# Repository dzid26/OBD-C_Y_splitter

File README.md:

# OBD-C Y-splitter
- compact size - 1x2.5cm
- possibility to add 120ohm CAN termination on CAN1 and CAN3 (note they can flip, so always terminate both)
- test points for sbu1 and sbu2

### Arrangement:
- Female-Male-Female - harness box has to be connected to J1 (as indicated by the arrow's origin)

Schematic:

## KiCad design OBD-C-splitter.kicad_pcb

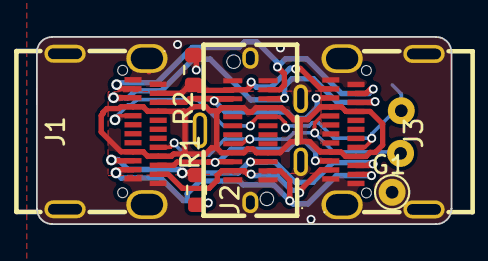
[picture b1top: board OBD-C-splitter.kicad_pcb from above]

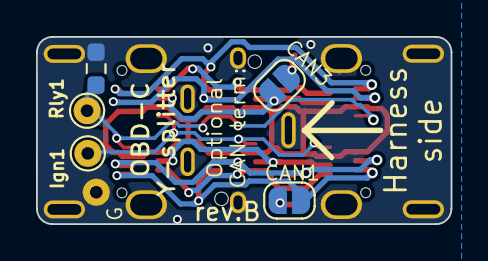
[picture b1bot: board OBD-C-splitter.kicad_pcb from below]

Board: 2 copper layers, 23.0 x 10.4 mm, 11 parts (5 on the bottom side), 14 nets.

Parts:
CAN1, CAN3: SolderJumper_2_Open; SolderJumper-2_P1.3mm_Open_RoundedPad1.0x1.5mm
G1: TestPoint; TestPoint_THTPad_D1.5mm_Drill0.7mm
Ign1: TestPoint; TestPoint_THTPad_D1.5mm_Drill0.7mm
J1, J3: Type-C Receptacle; TYPE-C-SMD_C9900025773
J2: Type-C Plug; USB-C-SMD_TYPEC-952-ACP24
R1, R2: 120R; R_0603_1608Metric
R3: 200; R_0603_1608Metric_Pad0.98x0.95mm_HandSolder
Rly1: TestPoint; TestPoint_THTPad_D1.5mm_Drill0.7mm

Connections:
/Sbu1: J1.B8 (SBU2), J2.B8 (SBU2), J3.A8 (SBU1), R3.1, Rly1.1
/Sbu2: Ign1.1, J1.A8 (SBU1), J2.A8 (SBU1), J3.B8 (SBU2)
/VBUS: J1.A4 (VBUS), J1.A9 (VBUS), J1.B4 (VBUS), J1.B9 (VBUS), J2.A4 (VBUS), J2.A9 (VBUS), J2.B4 (VBUS), J2.B9 (VBUS), J3.A4 (VBUS), J3.A9 (VBUS), J3.B4 (VBUS), J3.B9 (VBUS)
CAN0_H: J1.B11 (RX1+), J2.B11 (RX1+), J3.A2 (TX1+)
CAN0_L: J1.B10 (RX1-), J2.B10 (RX1-), J3.A3 (TX1-)
CAN1_H: CAN1.2 (B), J1.B2 (TX2+), J2.B2 (TX2+), J3.A11 (RX2+)
CAN1_L: J1.B3 (TX2-), J2.B3 (TX2-), J3.A10 (RX2-), R1.2
CAN2_H: J1.A11 (RX2+), J2.A11 (RX2+), J3.B2 (TX2+)
CAN2_L: J1.A10 (RX2-), J2.A10 (RX2-), J3.B3 (TX2-)
CAN3_H: J1.A2 (TX1+), J2.A2 (TX1+), J3.B11 (RX1+), R2.1
CAN3_L: CAN3.1 (A), J1.A3 (TX1-), J2.A3 (TX1-), J3.B10 (RX1-)
GND: G1.1, J1.A1 (GND), J1.A12 (GND), J1.B1 (GND), J1.B12 (GND), J1.S1 (SHIELD), J2.A1 (GND), J2.A12 (GND), J2.B1 (GND), J2.B12 (GND), J2.S1 (SHIELD), J3.A1 (GND), J3.A12 (GND), J3.B1 (GND), J3.B12 (GND), J3.S1 (SHIELD), R3.2
unnamed: CAN1.1 (A), R1.1
unnamed: CAN3.2 (B), R2.2

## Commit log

2025-10-07 added direction arrow
2025-10-29 Order matters
2025-11-04 Fixed CAN labels and termination resistors and sbu
